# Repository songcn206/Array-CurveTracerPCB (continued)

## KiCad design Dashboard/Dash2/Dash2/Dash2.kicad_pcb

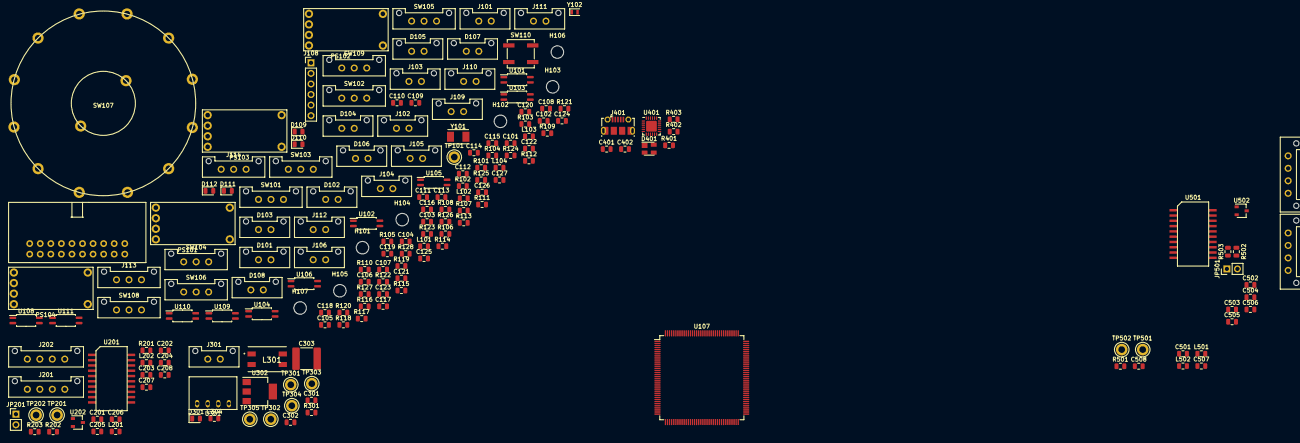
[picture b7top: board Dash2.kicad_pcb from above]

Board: 2 copper layers, 183 parts (0 on the bottom side), 120 nets, no tracks yet.

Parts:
C101, C102, C103, C104: 1u; C_0805_2012Metric
C105, C106, C109, C112, C113, C114, C115, C116, C117, C118, C119, C122, C123, C125: 100nF; C_0805_2012Metric
C107, C108: 4.3pF; C_0805_2012Metric
C110, C111: 2.2uF; C_0805_2012Metric
C120, C121: 2pF; C_0805_2012Metric
C124, C301, C401: 4.7uF; C_0805_2012Metric
C126, C127, C202, C203, C207, C402, C502, C503, C507: 0.1uF; C_0805_2012Metric
C201, C206, C302, C304, C501, C506: 10uF; C_0805_2012Metric
C204, C208, C504, C508: 0.01uF; C_0805_2012Metric
C205, C505: 0.22uF; C_0805_2012Metric
C303: 470pF; C_2220_5650Metric
D101: BPS_LED; Molex_MicroFit3.0_1x2xP3.00mm_PolarizingPeg_Vertical
D102: LeftSignal; Molex_MicroFit3.0_1x2xP3.00mm_PolarizingPeg_Vertical
D103: RightSignal; Molex_MicroFit3.0_1x2xP3.00mm_PolarizingPeg_Vertical
D104: KILL_SW_LED; Molex_MicroFit3.0_1x2xP3.00mm_PolarizingPeg_Vertical
D105: MOTOR-CONTACTOR; Molex_MicroFit3.0_1x2xP3.00mm_PolarizingPeg_Vertical
D106: MOTOR-PRECHARGE; Molex_MicroFit3.0_1x2xP3.00mm_PolarizingPeg_Vertical
D107: ARRAY-CONTACTOR; Molex_MicroFit3.0_1x2xP3.00mm_PolarizingPeg_Vertical
D108: ARRAY-PRECHARGE; Molex_MicroFit3.0_1x2xP3.00mm_PolarizingPeg_Vertical
D109, D110, D111, D112: D; D_0805_2012Metric
D301: PowerOn; LED_0805_2012Metric
D401: SP0503BAHT; SOT-143
H101, H102, H103, H104, H105, H106, H107: MountingHole; MountingHole_3mm
J101: Left_Signal; Molex_MicroFit3.0_1x2xP3.00mm_PolarizingPeg_Vertical
J102: Right_Signal; Molex_MicroFit3.0_1x2xP3.00mm_PolarizingPeg_Vertical
J103: Brake Light; Molex_MicroFit3.0_1x2xP3.00mm_PolarizingPeg_Vertical
J104: Headlight; Molex_MicroFit3.0_1x2xP3.00mm_PolarizingPeg_Vertical
J105: Backup; Molex_MicroFit3.0_1x2xP3.00mm_PolarizingPeg_Vertical
J106: BPS_PWR; Molex_MicroFit3.0_1x2xP3.00mm_PolarizingPeg_Vertical
J107: Gecko_Cable; ribbon_cable_right_2x10
J108: JTAG; PinHeader_1x06_P2.54mm_Vertical
J109: Motor-C; Molex_MicroFit3.0_1x2xP3.00mm_PolarizingPeg_Vertical
J110: Motor-P; Molex_MicroFit3.0_1x2xP3.00mm_PolarizingPeg_Vertical
J111: Array-C; Molex_MicroFit3.0_1x2xP3.00mm_PolarizingPeg_Vertical
J112: Array-P; Molex_MicroFit3.0_1x2xP3.00mm_PolarizingPeg_Vertical
J113, J114: Conn_01x03_Female; Molex_MicroFit3.0_1x3xP3.00mm_PolarizingPeg_Vertical
J201, J501: CAN_IN; Molex_MicroFit3.0_1x4xP3.00mm_PolarizingPeg_Vertical
J202, J502: CAN_OUT; Molex_MicroFit3.0_1x4xP3.00mm_PolarizingPeg_Vertical
J301: CarPowerConnector; Molex_MicroFit3.0_1x2xP3.00mm_PolarizingPeg_Vertical
J401: USB_B_Micro; USB_Micro-B_Molex-105017-0001
JP201, JP501: Termination Resistors; PinHeader_1x02_P2.54mm_Vertical
L101, L102, L103, L104: 22u; L_0805_2012Metric
L201, L202, L501, L502: 2kH; L_0805_2012Metric
L301: SRF0905-100Y; SRF0905A
PS101, PS102, PS103, PS104: RCD-24
R101, R102, R103, R107, R108, R116, R125, R126, R127, R128: 10k; R_0805_2012Metric
R104, R105: 4.9k; R_0805_2012Metric
R106, R113: 1.2k; R_0805_2012Metric
R109, R110, R111, R112: 105; R_0805_2012Metric
R114, R115, R117, R118, R119, R120: 330R; R_0805_2012Metric
R121, R122, R123, R124: 105R; R_0805_2012Metric
R201, R501: 0; R_0805_2012Metric
R202, R203, R502, R503: 60; R_0805_2012Metric
R301: 1.5k; R_0805_2012Metric
R401: 22.1k; R_0805_2012Metric
R402: 47.5k; R_0805_2012Metric
R403: 1k; R_0805_2012Metric
SW101: CRUISE_SET; Molex_MicroFit3.0_1x3xP3.00mm_PolarizingPeg_Vertical
SW102: CRUISE; Molex_MicroFit3.0_1x3xP3.00mm_PolarizingPeg_Vertical
SW103: HAZARD; Molex_MicroFit3.0_1x3xP3.00mm_PolarizingPeg_Vertical
SW104: HEADLIGHT_SW; Molex_MicroFit3.0_1x3xP3.00mm_PolarizingPeg_Vertical
SW105: F/R_SW; Molex_MicroFit3.0_1x3xP3.00mm_PolarizingPeg_Vertical
SW106: BACKUP_SW; Molex_MicroFit3.0_1x3xP3.00mm_PolarizingPeg_Vertical
SW107: SW_Rotary2x6; CK1035
SW108: TURN_SIGNAL_SW; Molex_MicroFit3.0_1x3xP3.00mm_PolarizingPeg_Vertical
SW109: KILL_SW; Molex_MicroFit3.0_1x3xP3.00mm_PolarizingPeg_Vertical
SW110: RESET; SW_SPST_B3SL-1002P
TP101: POWER; TestPoint_Keystone_5005-5009_Compact
TP201, TP501: CAN_H; TestPoint_Keystone_5005-5009_Compact
TP202, TP502: CAN_L; TestPoint_Keystone_5005-5009_Compact
TP301: +12V_TP; TestPoint_Keystone_5005-5009_Compact
TP302: GNDPWR_TP; TestPoint_Keystone_5005-5009_Compact
TP303: +5V_TP; TestPoint_Keystone_5005-5009_Compact
TP304: GND_TP; TestPoint_Keystone_5005-5009_Compact
TP305: +3.3V_TP; TestPoint_Keystone_5005-5009_Compact
U101, U102, U103, U104, U105, U106, U108, U109, U110, U111: EL3H7; SOP-4_4.4x2.6mm_P1.27mm
U107: STM32F413ZHTx; LQFP-144_20x20mm_P0.5mm
U201, U501: ADM3055E; SOIC-20W_7.5x15.4mm_Pitch1.27mm
U202, U502: CDSOT23-T24CAN; SOT-23W
U301: RI3-1205S; RI3_DC_Converter
U302: NCP1117-3.3_SOT223; SOT-223-3_TabPin2
U401: CP2102N-A01-GQFN24; QFN-24-1EP_4x4mm_P0.5mm_EP2.6x2.6mm
Y101: Crystal; Crystal_SMD_TXC_7A-2Pin_5x3.2mm
Y102: Crystal; Crystal_SMD_TXC_9HT11-2Pin_2.0x1.2mm

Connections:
+3V3: C105.1, C109.1, C112.1, C113.1, C114.1, C115.1, C116.1, C117.1, C118.1, C119.1, C122.1, C123.1, C124.1, C125.1, C203.1, C204.1, C304.1, C401.1, C402.1, C503.1, C504.1, D109.1, D111.1, J107.11, J108.6, J113.1, J114.1, R101.2, R102.2, R103.2, R104.1, R105.1, R107.1, R108.1, R114.1, R115.1, R403.1, SW104.3, SW105.3, TP305.1, U107.6, U107.17, U107.30, U107.32, U107.33, U107.39, U107.52, U107.62, U107.72, U107.84, U107.95, U107.108, U107.121, U107.131, U107.143, U107.144, U201.4, U302.2, U401.5, U401.6, U401.7, U501.4
+5V: C201.1, C202.1, C302.1, C303.2, C501.1, C502.1, R301.1, TP303.1, U201.3, U301.4, U302.3, U501.3
+12V: C101.2, C102.2, C103.2, C104.2, C301.1, J301.1, L101.2, L102.2, L103.2, L104.2, L301.1, L301.2, SW106.3, SW109.2, TP301.1, U103.4, U104.4, U105.4, U106.4
/A_CNCTR: R119.2, R123.2, U107.137
/A_PRCHG: R120.2, R124.2, U107.136
/BK_LGHT: R111.2, U107.42
/BPS_PWR: J106.1, R106.1, SW107.1, SW107.2, SW107.3, SW107.4, SW107.5
/Backup: J105.1, SW106.2
/Brake_Pot: C127.1, D111.2, D112.1, R126.2, R128.2, U107.37
/CRUZ_EN: SW102.2, U107.53
/CRUZ_ST: SW101.2, U107.54
/CarCAN/CAN_H: J201.3, J202.3, R202.2, TP201.1, U201.14, U202.1
/CarCAN/CAN_L: J201.4, J202.4, R203.2, TP202.1, U201.13, U202.2
/CarCAN/CAN_RX: U107.114, U201.5
/CarCAN/CAN_TX: U107.115, U201.7
/CarCAN/RSlope: R201.1, U201.12
/CarCAN/TERM_H: JP201.2, R202.1
/CarCAN/TERM_L: JP201.1, R203.1
/FR_SW: SW105.2, U107.139
/HZD_SW: SW103.2, U107.60
/HeadlightPWR: R112.2, SW104.2
/IG1: R104.2, U101.4, U107.75
/IG2: R105.2, U102.4, U107.76
/JTDI: J108.2, U107.110
/JTDO: J108.3, U107.133
/LEFT_SW: R108.2, SW108.3, U107.55
/L_LGHT: D102.1, R109.2, U107.41
/M_CNCTR: R117.2, R121.2, U107.135
/M_PRCHG: R118.2, R122.2, U107.134
/MotorCAN/CAN_H: J501.3, J502.3, R502.2, TP501.1, U501.14, U502.1
/MotorCAN/CAN_L: J501.4, J502.4, R503.2, TP502.1, U501.13, U502.2
/MotorCAN/CAN_RX: U107.73, U501.5
/MotorCAN/CAN_TX: U107.74, U501.7
/MotorCAN/RSlope: R501.1, U501.12
/MotorCAN/TERM_H: JP501.2, R502.1
/MotorCAN/TERM_L: JP501.1, R503.1
/NRST: C106.1, SW110.2, U107.25
/RIGHT_SW: R107.2, SW108.1, U107.66
/R_LGHT: D103.1, R110.2, U107.36
/Regen_Pot: C126.1, D109.2, D110.1, R125.2, R127.2, U107.26
/SWCLK: J108.4, U107.109
/SWDIO: J108.1, U107.105
/USB/UART_RX: U107.77, U401.20
/USB/UART_TX: U107.78, U401.21
GND: C105.2, C106.2, C107.2, C108.2, C109.2, C110.2, C111.2, C112.2, C113.2, C114.2, C115.2, C116.2, C117.2, C118.2, C119.2, C120.1, C121.2, C122.2, C123.2, C124.2, C125.2, C126.2, C127.2, C201.2, C202.2, C203.2, C204.2, C302.2, C304.2, C401.2, C402.2, C501.2, C502.2, C503.2, C504.2, D105.1, D106.1, D107.1, D108.1, D110.2, D112.2, D301.1, D401.1, J107.1, J108.5, J113.3, J114.3, J401.5, J401.6, R116.2, R125.1, R126.1, R402.2, SW101.1, SW102.1, SW103.1, SW104.1, SW105.1, SW108.2, SW110.1, TP304.1, U101.3, U102.3, U103.2, U104.2, U105.2, U106.2, U107.16, U107.31, U107.38, U107.51, U107.61, U107.83, U107.94, U107.107, U107.120, U107.130, U108.2, U109.2, U110.2, U111.2, U201.1, U201.2, U201.10, U301.3, U302.1, U401.2, U401.25, U501.1, U501.2, U501.10
GNDPWR: C101.1, C102.1, C103.1, C104.1, C301.2, D101.1, D104.1, J105.2, J106.2, J301.2, PS101.4, PS102.4, PS103.4, PS104.4, SW106.1, TP302.1, U101.2, U102.2, U301.1
unnamed: C107.1, U107.23, Y101.2
unnamed: C108.1, U107.24, Y101.1
unnamed: C110.1, U107.71
unnamed: C111.1, U107.106
unnamed: C120.2, U107.8, Y102.1
unnamed: C121.1, U107.9, Y102.2
unnamed: C205.1, L201.2, U201.19
unnamed: C205.2, L202.2, U201.18, U201.20
unnamed: C206.1, C207.1, C208.1, J201.1, J202.1, L201.1, U201.16
unnamed: C206.2, C207.2, C208.2, J201.2, J202.2, L202.1, R201.2, U201.11, U201.15, U202.3
unnamed: C303.1, L301.3, L301.4, U301.2
unnamed: C505.1, L501.2, U501.19
unnamed: C505.2, L502.2, U501.18, U501.20
unnamed: C506.1, C507.1, C508.1, J501.1, J502.1, L501.1, U501.16
unnamed: C506.2, C507.2, C508.2, J501.2, J502.2, L502.1, R501.2, U501.11, U501.15, U502.3
unnamed: D101.2, R106.2
unnamed: D102.2, R114.2
unnamed: D103.2, R115.2
unnamed: D104.2, R113.2
unnamed: D105.2, R117.1
unnamed: D106.2, R118.1
unnamed: D107.2, R119.1
unnamed: D108.2, R120.1
unnamed: D301.2, R301.2
unnamed: D401.2, J401.1, R401.2
unnamed: D401.3, J401.2, U401.4
unnamed: D401.4, J401.3, U401.3
unnamed: J101.1, PS101.5
unnamed: J101.2, PS101.6
unnamed: J102.1, PS102.5
unnamed: J102.2, PS102.6
unnamed: J103.1, PS103.5
unnamed: J103.2, PS103.6
unnamed: J104.1, PS104.5
unnamed: J104.2, PS104.6
unnamed: J107.16, U107.58
unnamed: J107.17, U107.59
unnamed: J109.1, U108.4
unnamed: J109.2, U108.3
unnamed: J110.1, U109.4
unnamed: J110.2, U109.3
unnamed: J111.1, U110.4
unnamed: J111.2, U110.3
unnamed: J112.1, U111.4
unnamed: J112.2, U111.3
unnamed: J113.2, R127.1
unnamed: J114.2, R128.1
unnamed: L101.1, PS101.1
unnamed: L102.1, PS102.1
unnamed: L103.1, PS103.1
unnamed: L104.1, PS104.1
unnamed: PS101.3, U103.3
unnamed: PS102.3, U104.3
unnamed: PS103.3, U105.3
unnamed: PS104.3, U106.3
unnamed: R101.1, SW101.3
unnamed: R102.1, SW102.3
unnamed: R103.1, SW103.3
unnamed: R109.1, U103.1
unnamed: R110.1, U104.1
unnamed: R111.1, U105.1
unnamed: R112.1, U106.1
unnamed: R113.1, SW109.1
unnamed: R116.1, U107.138
unnamed: R121.1, U108.1
unnamed: R122.1, U109.1
unnamed: R123.1, U110.1
unnamed: R124.1, U111.1
unnamed: R401.1, R402.1, U401.8
unnamed: R403.2, U401.9
unnamed: SW107.7, SW107.8, SW107.9, U102.1
unnamed: SW107.10, U101.1
unnamed: SW107.11, TP101.1
unnamed: SW107.13, SW107.14, SW109.3

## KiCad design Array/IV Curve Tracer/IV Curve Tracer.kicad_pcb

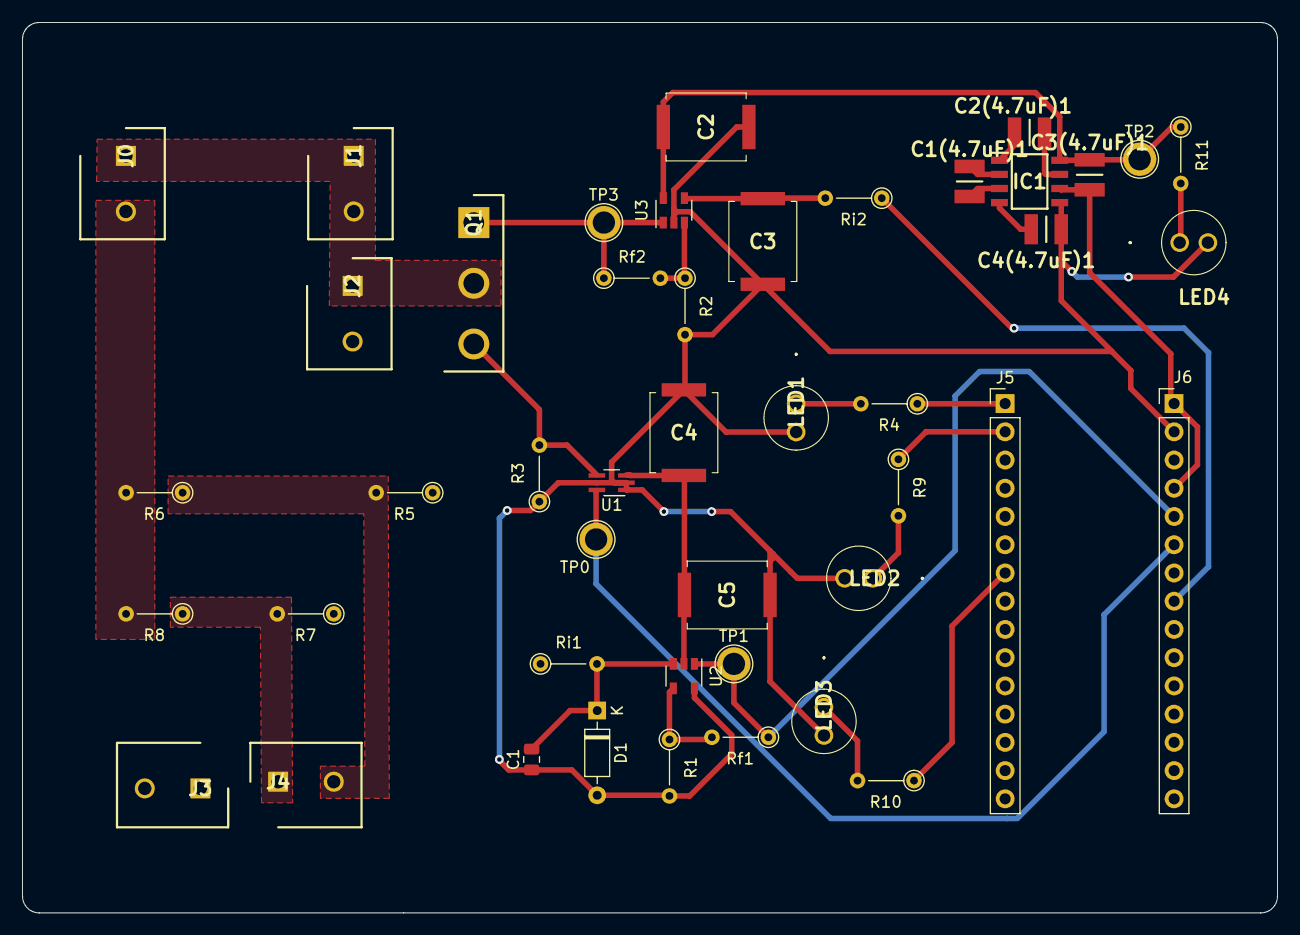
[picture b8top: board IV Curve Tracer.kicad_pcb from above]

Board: 2 copper layers, 112.9 x 80.1 mm, 45 parts (0 on the bottom side), 29 nets.

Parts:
C1: Variable; C_0805_2012Metric
C1(4.7uF)1, C2(4.7uF)1, C3(4.7uF)1, C4(4.7uF)1: HMK325C7475KM-PE (4.7uF); CAPC3225X270N
C2, C3, C4, C5: SMDTC04100TA00JS00
D1: 1N5226B-B; D_DO-35_SOD27_P7.62mm_Horizontal
IC1: MAX680ESA+; SOIC127P600X175-8N
J0, J1, J2, J3, J4: TB002-500-02BE; SHDR2W100P0X500_1X2_1000X760X1040P
J5, J6: Conn_01x15; PinHeader_1x15_P2.54mm_Vertical
LED1, LED2, LED3, LED4: TLHR5400-AS12Z; TLHR5400AS12Z
Q1: IRF100P218XKMA1; TO546P531X1558X2499-3P
R1, R2: 1k; R_Axial_DIN0204_L3.6mm_D1.6mm_P5.08mm_Vertical
R3: .5m; R_Axial_DIN0204_L3.6mm_D1.6mm_P5.08mm_Vertical
R4, R9, R10, R11: 330; R_Axial_DIN0204_L3.6mm_D1.6mm_P5.08mm_Vertical
R5: 56.6k; R_Axial_DIN0204_L3.6mm_D1.6mm_P5.08mm_Vertical
R6: 10k; R_Axial_DIN0204_L3.6mm_D1.6mm_P5.08mm_Vertical
R7: 132K; R_Axial_DIN0204_L3.6mm_D1.6mm_P5.08mm_Vertical
R8: 2k; R_Axial_DIN0204_L3.6mm_D1.6mm_P5.08mm_Vertical
Rf1: 1k; R_Axial_DIN0204_L3.6mm_D1.6mm_P5.08mm_Vertical
Rf2: 4k; R_Axial_DIN0204_L3.6mm_D1.6mm_P5.08mm_Vertical
Ri1: 10k; R_Axial_DIN0204_L3.6mm_D1.6mm_P5.08mm_Vertical
Ri2: 1k; R_Axial_DIN0204_L3.6mm_D1.6mm_P5.08mm_Vertical
TP0, TP1, TP2, TP3: TestPoint; TestPoint_Plated_Hole_D2.0mm
U1: INA211CQDCKRQ1; SOT-363_SC-70-6_Handsoldering
U2, U3: LT1215; SOT-23-5

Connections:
+3V3: C4.1, C5.1, U1.3, U2.2
+5V: C3(4.7uF)1.2, IC1.6, J6.1, J6.4
+10V: C2.2, C3(4.7uF)1.1, IC1.8, R11.1, TP2.1, U3.5
-10V: C4(4.7uF)1.1, IC1.4
ADC_C: J6.6, TP0.1, U1.6
ADC_V: J6.5, Rf1.1, TP1.1, U2.1
DAC_Control: J6.8, Ri2.1
GATE: Q1.1, Rf2.1, TP3.1, U3.1
GND: C1.1, C2.1, C3.2, C4.2, C4(4.7uF)1.2, C5.2, D1.2, IC1.5, J6.2, LED1.2, LED2.2, LED3.2, LED4.2, R1.2, R2.2, R3.1, U1.1, U1.2, U1.5, U2.5, U3.2
GNDA: J0.2, R6.2, R8.2
unnamed: C1(4.7uF)1.1, IC1.3
unnamed: C1(4.7uF)1.2, IC1.2
unnamed: C1.2, D1.1, Ri1.2, U2.3
unnamed: C2(4.7uF)1.1, IC1.1
unnamed: C2(4.7uF)1.2, IC1.7
unnamed: C3.1, Ri2.2, U3.4
unnamed: J0.1, J1.1, J1.2, J2.1, Q1.2
unnamed: J4.1, R7.2, R8.1
unnamed: J4.2, R5.2, R6.1
unnamed: J5.1, R4.1
unnamed: J5.2, R9.1
unnamed: J5.7, R10.1
unnamed: LED1.1, R4.2
unnamed: LED2.1, R9.2
unnamed: LED3.1, R10.2
unnamed: LED4.1, R11.2
unnamed: Q1.3, R3.2, U1.4
unnamed: R1.1, Rf1.2, U2.4
unnamed: R2.1, Rf2.2, U3.3

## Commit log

2019-03-02 Test for austin branch
2019-03-02 KiCad Schematic for Display
2020-02-22 Layout the dashboard v2
2020-02-23 Add complete layout of the board
2020-05-12 Add LED board and timing circuitry. The LED board is not yet integrated with the Dash.
2020-06-06 Make major changes to Dashboard and file structure.
    Problem
    =======
    * The dashboard needs to be redesigned. These are continuing changes
    to Dashboard 2.0.
    * There are way too many files cluttering the Dashboard folder.
    * We need to include LED indicators for the driver that make sense.
2020-06-06 Change the MCU to the R (64-pin) variant.
    Problem
    =======
    I don't want to have to solder 144 pins.
    Solution
    ========
    I changed the package of the MCU to the 64-pin
2020-06-06 Fixed minor issues and updated the pinout doc.
2020-06-06 Fix formatting on README.md
2020-06-09 Added footprint and symbol for Bluetooth module we will be using.
2020-06-09 Added symbol to PCB editor. Wasn't saved last commit.
2020-06-10 Created new sheet for bluetooth module. Using pins 37 and 38 of STM for UART communication with module. May need others to configure bluetooth module for low power mode.
2020-06-10 Added annotations to all schematic symbols. Ran electrical rules check. Need to figure out how to connect pins between sheets. Added reset circuit and finished reverse voltage protection circuit. Nee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
2020-06-11 Connected hierarchial sheets. Added text for all status led's.
2020-06-11 Added PWM for fan control. Since max output of pins are 3V, used buttons to connect 12V to fan. Used pin 28 of STM for PWM using Low Power Timer 1.
2020-06-11 Added UART_TX indicator light.
2020-06-11 The setup for bluetooth mode can't be done through a port using the STM so I used a switch instead, we can use that to toggle between Application mode and testing mode.
2020-06-11 Changed resistor values
2020-06-13 Changed UART to UART 1 because it also had CTS and RTS pins
2020-06-13 Added CTS and RTS connections because we will be sending lots of bytes at a time with the module
2020-06-14 Added Interface Pins to Misc sheet so we don't have to make a revision every time we want to add something. Also fixed the input/output for the hierarchial labels.
2020-06-19 Add redundant potentiometers and relabel components.
2020-06-22 Added button to change strobelight pulsing pattern.
2020-06-25 Removed the reverse voltage protection circuit because we are not powering it with an external source
2020-06-25 Connected bluetooth module symbol to footprint and made all library paths relative.
2020-06-25 Assigned footprints to all symbols except reset circuit(high voltage detector). Changed 18 pin connector to 3, 6 pin connectors. Generated netlist.
2020-06-25 Made file paths of symbol libraries relative. Added footprint for high voltage detection that is SMD and has same specs as one recommended in Bluetooth Module datasheet.
2020-06-28 Created new board for Bluetooth module because the antenna cannot have a ground plane on it. Made everything connect using pin headers. Will mount the Bluetooth module board onto the Master board.
2020-06-30 Finished adding interface pins to master board. For some reason, the mosfet track isn't letting me connect to the fan power. I'm not sure why all these schematics are listed as modified because I did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
2020-07-02 Finished master board. Working to make sure that bluetooth mount won't cover anything important on master board, yet still be big enough to hold everything.
2020-07-02 Finished Bluetooth board. Entire board wouldn't fit inside mount so the board is extended past the mounting holes. Still need to replace footprint of interface pins with connectors that go through th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
2020-07-02 Added references to board
2020-07-02 Added signature
2020-07-03 Connected power to Bluetooth Module
2020-07-11 Finished fan board
2020-07-11 Finished schematic for Fan Board:)
2020-07-11 Finished PCB
2020-07-11 Adds current board project
2020-07-11 Found footprint and symbol
2020-07-11 Extract the MPPT tracer files into Array folder.
    This just moves the MPPT tracer files to the Array folder so that
    our version control can work slightly better.
2020-07-14 Finished basic connections. Still need to add DC-DC converter and connection for interrupts if needed.
2020-07-14 Added connections for control, pwr, and ground. Need to add DC-DC converter for 12V to 5V
2020-07-15 Added DCDC converter for 12V-5V power supply
2020-07-16 Creates fan brd interface schematics and updates symbols/footprints related to the leader board
2020-07-17 Finishes schematics for bps leader board
2020-07-17 Renames bps master to bps leader:
2020-07-17 Places most components of leader board in their respective locations with nothing traced
2020-07-18 Adds power planes
2020-07-20 Everything traced in leader board except for power circuitry
2020-07-25 Traces power components
2020-07-25 Removed dc converter and power connectors.
2020-07-25 Changed Leader board connections and changed footprints of fan connections to molex 3mm
2020-07-25 Aesthetic changes
2020-07-25 Changed diodes used to cheaper ones
2020-07-25 Finished leader board
2020-07-25 Completes schematic of current board
2020-07-25 Adds AS8510 into utsvt-bps.lib
2020-07-25 Edits name of mounting holes to standardized M3 screw size
2020-07-25 Updates footprint for 470pF capacitor
2020-07-25 Completes current board schematic and starts PCB
2020-07-25 Simplifies dc-dc converter schematics
2020-07-25 Finished Fan Board PCB
2020-07-25 Organizes and edits PCB layout
2020-07-25 Worked on layout of board
2020-07-26 Updates leader board, need to add comments
2020-07-26 Finishes new power circuitry tracing
2020-07-26 Adds version number to leader_board and creates schematics pdf
2020-07-26 Finishes PCB layout of current board
2020-07-26 Redid layout of board
2020-07-26 Finishing touches
2020-07-27 Added status LED
2020-07-27 Added silkscreen comments
2020-07-27 Removed bluetooth board
2020-08-01 Reverts edited files that are not related to the FanBoard back to master branch's versions
2020-08-01 Deletes bluetooth symbols/footprints. Already exists on leader_board branch
2020-08-01 Removes SOT-23 footprint that was added into the BPS library because it already exists in the kicad libraries
2020-08-01 Edits diode V2F22HM footprint to not have a copper cutout
2020-08-01 Moves flyback diode V2F22HM footprint to Common library instead of UTSVT_BPS.pretty because other systems can/will use this component besides the BPS
2020-08-01 Adds copper cutout to transformer for isospi because ltc6820 datasheet recommended it
2020-08-01 Changed location of diodes and direction of status LED. Fixed value and reference labels of components, made pwrgnd plane bigger, and made distance of mounting holes on both sides symmetrical.
2020-08-02 Changes LTC6820 POL and PHA pins to +5V due to VIH and VIL parameters in datasheet
2020-08-02 Checks and make sure everything passes DRC
2020-08-02 Updates V2F22HM footprint to include polarity indicator on silkscreen
2020-08-02 Changes diode footprints to correct path. Need to update netlist and pcb file
2020-08-02 Adds documents/pdfs to leader board
2020-08-02 Adds keepout zone for the transformer and the dimensions
2020-08-02 Deletes errenous pdf
2020-08-02 Fixes unconnection error of pcb
2020-08-02 Checks ERC/DRC one more time
2020-08-02 Edits LTC6820 symbol, generates netlist, and fixes schematic errors
2020-08-02 Creates PDF of schematic
2020-08-02 Edits BPS symbol library
2020-08-02 Updates netlist
2020-08-02 Updates LTC6820 symbol
2020-08-02 Removes previous current board interface hierachy sheet
2020-08-02 These twwo files were combined into SensorBrdInterface.sch
2020-08-02 Deletes unnecessary AS8510 file
2020-08-02 Changed bottom copper layer size
2020-08-02 Set up for separate repo
